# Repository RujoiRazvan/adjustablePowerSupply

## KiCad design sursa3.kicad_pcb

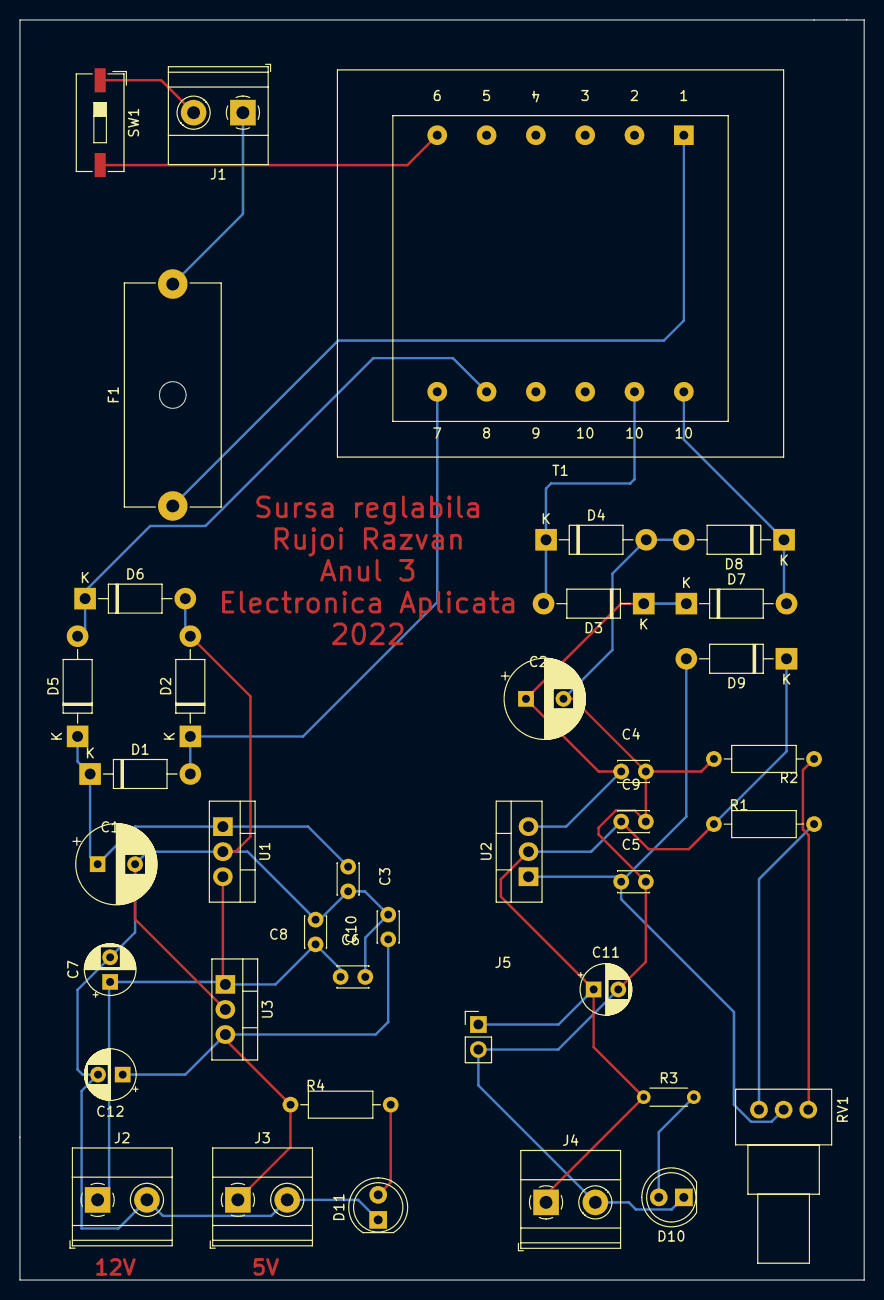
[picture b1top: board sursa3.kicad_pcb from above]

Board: 2 copper layers, 85.6 x 127.8 mm, 39 parts (0 on the bottom side), 20 nets.

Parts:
C1, C2: 2200uF; CP_Radial_D8.0mm_P3.80mm
C3, C4, C5, C6, C8, C9, C10: 100nF; C_Disc_D3.0mm_W2.0mm_P2.50mm
C7, C11, C12: 100uF; CP_Radial_D5.0mm_P2.50mm
D1, D2, D3, D4, D5, D6, D7, D8, D9: 1N4002; D_DO-41_SOD81_P10.16mm_Horizontal
D10, D11: LED; LED_D5.0mm
F1: Fuse; Fuseholder_Cylinder-5x20mm_Schurter_0031_8201_Horizontal_Op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
J1, J2, J3, J4: Screw_Terminal_01x02; TerminalBlock_Phoenix_MKDS-1,5-2_1x02_P5.00mm_Horizontal
J5: Screw_Terminal_01x02; PinHeader_1x02_P2.54mm_Vertical
R1: 120R; R_Axial_DIN0207_L6.3mm_D2.5mm_P10.16mm_Horizontal
R2: 100R; R_Axial_DIN0207_L6.3mm_D2.5mm_P10.16mm_Horizontal
R3: 1k; R_Axial_DIN0204_L3.6mm_D1.6mm_P5.08mm_Horizontal
R4: 300R; R_Axial_DIN0207_L6.3mm_D2.5mm_P10.16mm_Horizontal
RV1: 1k; Potentiometer_Alps_RK09Y11_Single_Horizontal
SW1: SW_DIP_x01; SW_DIP_SPSTx01_Slide_9.78x4.72mm_W8.61mm_P2.54mm
T1: Transformer_1P_2S; Transformer_Breve_TEZ-38x45
U1: LM7812_TO220; TO-220-3_Vertical
U2: LM317_TO-220; TO-220-3_Vertical
U3: LM7805_TO220; TO-220-3_Vertical

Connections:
/3: D1.2, D2.1, T1.3
unnamed: C1.1, C3.1, D1.1, D5.1, U1.1
unnamed: C1.2, C3.2, C6.2, C7.2, C8.2, C10.2, C12.2, D2.2, D6.2, D11.1, J2.2, J3.2, U1.2, U3.2
unnamed: C2.1, C4.1, D3.1, D7.1, U2.3
unnamed: C5.1, D9.2, RV1.2, U2.1
unnamed: C6.1, C7.1, C8.1, J2.1, U1.3, U3.1
unnamed: C10.1, C12.1, J3.1, R4.1, U3.3
unnamed: C9.1, C11.1, D9.1, J4.1, J5.1, R1.1, R3.1, U2.2
unnamed: C2.2, C4.2, C5.2, C9.2, C11.2, D4.2, D8.2, D10.1, J4.2, J5.2, R2.2
unnamed: D3.2, D4.1, T1.5
unnamed: D5.2, D6.1, T1.4
unnamed: D7.2, D8.1, T1.6
unnamed: D10.2, R3.2
unnamed: D11.2, R4.2
unnamed: F1.1, T1.1
unnamed: F1.2, J1.1
unnamed: J1.2, SW1.1
unnamed: R1.2, RV1.1
unnamed: R2.1, RV1.3
unnamed: SW1.2, T1.2
